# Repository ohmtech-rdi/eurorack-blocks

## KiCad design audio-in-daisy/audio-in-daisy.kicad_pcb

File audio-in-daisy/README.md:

# audio-in-daisy

## Description

This block is a simple analog audio input for the
[Daisy Seed](https://www.electro-smith.com/daisy/daisy) onboard codec.
Its design is detailed [here](./documentation/design.md).

## Connecting

- This block needs its `GND` to be connected to the ground. All `GND` pins are connected
   internally,
- This block needs its `-12` to be connected to the `-12V` of the `power-bus`,
- This block needs its `+12` to be connected to the `+12V` of the `power-bus`,
- The `NOP` pin can be either connected to:
   - `GND` to send (slightly noisy) zeros to the software implementation,
   - Cascading the `DI` signal from another `audio-in-daisy` block,
   - A pseudo-random predefined signal to detect a jack connection
      as explained on the Mutable Instruments forums
      [here](https://forum.mutable-instruments.net/t/plaits-normalization-probe/14358/2)
      and implemented
      [here](https://github.com/pichenettes/eurorack/blob/master/plaits/ui.cc#L368).
- The signal `OUT` is the audio input signal. It should be connected to either Pin 16 or Pin 17.
   See [Daisy Seed pinout](https://images.squarespace-cdn.com/content/v1/58d03fdc1b10e3bf442567b8/1591827747342-HCXMM2NNR26SP5F4U2CJ/ke17ZwdGBToddI8pDm48kN5PbQBGNYbW-5Hm1pf8hRF7gQa3H78H3Y0txjaiv_0fDoOvxcdMmMKkDsyUqMSsMWxHk725yiiHCCLfrh8O1z4YTzHvnKhyp6Da-NYroOW3ZGjoBKy3azqku80C789l0kLp48N9LluBiCpBrPZntaz462IffsVrAff3VJkwKncM1HZuDnV98dfxM9yHlqFkUQ/DaisyPinoutRev4%404x.png?format=500w) for details.

If only one audio input is connected, the other unused pin should be connected to `GND`.

The `DI` pin is the signal coming out directly from the jack connector and should be left floating
if not used.

The pseudo-random predefined signal jack detection method allows,
from a user experience point of view, to dissociate a non-connected
jack from a connected jack at `GND` level.

## Using

```c++
int main ()
{
   using namespace erb;
   
   Module module;
   AudioInDaisy audio_in_left (module, AudioInDaisyPinLeft);   // 1.
   AudioInDaisy audio_in_right (module, AudioInDaisyPinRight); // 2.

   module.run ([&](){
      for (size_t i = 0 ; i < audio_in_left.size () ; ++i)     // 3.
      {
         float left  = audio_in_left [i];                      // 4.
         float right = audio_in_right [i];                     // 5.
      }
   });
}
```

1. Attach the audio input to the module with the onboard codec left pin (Pin 16),
2. Attach the audio input to the module with the onboard codec right pin (Pin 17),
2. Loop through all the samples in the buffer. `erb::buffer_size` can be used instead,
3. Retrieve the audio input value on codec left pin,
4. Retrieve the audio input value on codec right pin.

The `AudioInDaisy` class reference is available [here](./documentation/reference.md).

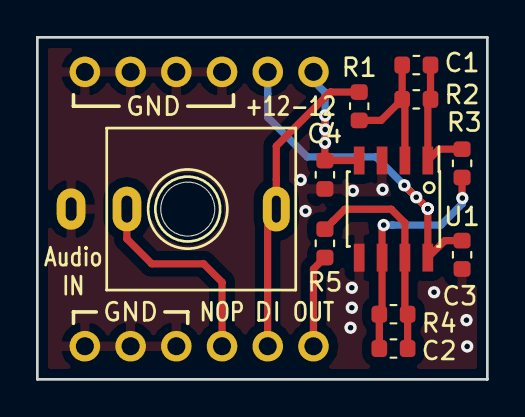
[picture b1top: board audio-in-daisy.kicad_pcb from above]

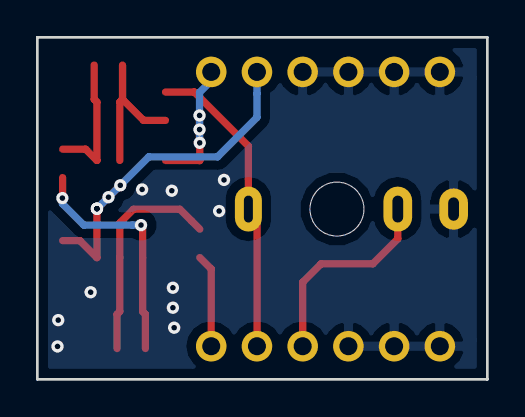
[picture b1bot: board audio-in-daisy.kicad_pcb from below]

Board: 2 copper layers, 25.0 x 19.0 mm, 13 parts (2 on the bottom side), 10 nets.

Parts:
C1: 47p; C_0603_1608Metric
C2: 560p; C_0603_1608Metric
C3, C4: 100n; C_0603_1608Metric
J1: IN; ThonkiconnJack
J2: OUT; PinHeader_1x06_P2.54mm_Vertical
J3: POWER; PinHeader_1x06_P2.54mm_Vertical
R1, R2, R3: 100k; R_0603_1608Metric
R4: 10k; R_0603_1608Metric
R5: 1k; R_0603_1608Metric
U1: TL072; SOIC-8_3.9x4.9mm_P1.27mm

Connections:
+12V: C3.1, J3.5, U1.8
-12V: C4.2, J3.6, U1.4
DI: J1.T, J2.2, R1.2
GND: C3.2, C4.1, J1.S, J2.4, J2.5, J2.6, J3.1, J3.2, J3.3, J3.4, U1.3, U1.5
NOP: J1.TN, J2.3
unnamed: C1.1, R2.1, R3.2, U1.1
unnamed: C1.2, R1.1, R2.2, U1.2
unnamed: C2.1, R4.1, R5.2, U1.7
unnamed: C2.2, R3.1, R4.2, U1.6
OUT: J2.1, R5.1

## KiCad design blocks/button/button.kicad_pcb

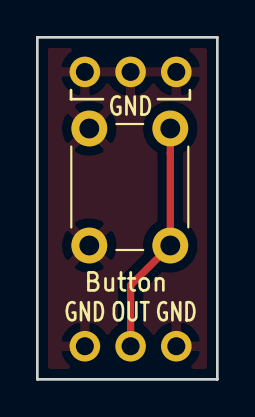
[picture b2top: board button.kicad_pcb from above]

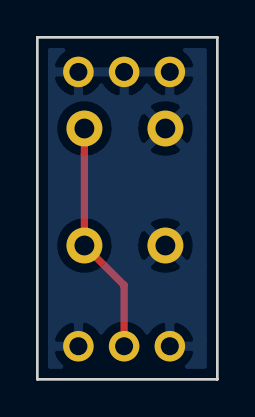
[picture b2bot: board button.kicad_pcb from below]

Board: 2 copper layers, 10.0 x 19.0 mm, 3 parts (2 on the bottom side), 2 nets.

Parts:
J1: POWER; PinHeader_1x03_P2.54mm_Vertical
J2: OUT; PinHeader_1x03_P2.54mm_Vertical
SW1: SW_Push_Dual; SW_PUSH_6mm_H7.3mm

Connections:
GND: J1.1, J1.2, J1.3, J2.1, J2.3, SW1.1
OUT: J2.2, SW1.2

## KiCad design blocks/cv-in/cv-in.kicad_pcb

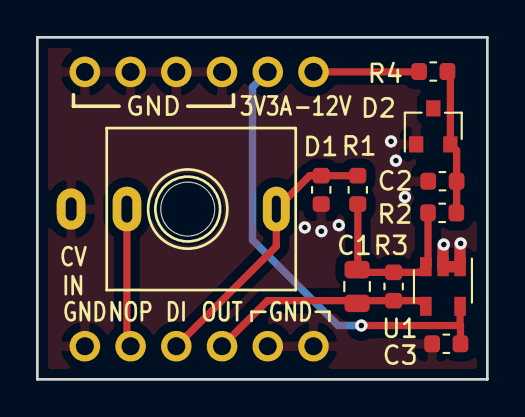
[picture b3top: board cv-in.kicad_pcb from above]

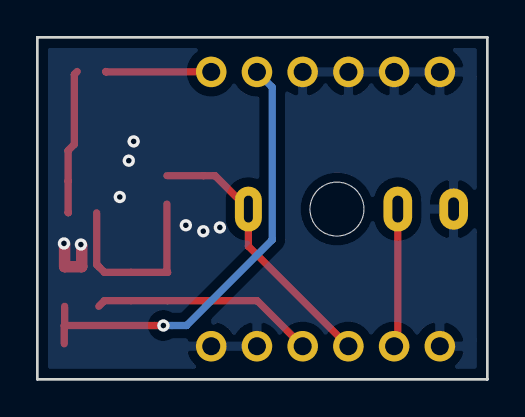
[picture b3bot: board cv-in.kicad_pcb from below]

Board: 2 copper layers, 25.0 x 19.0 mm, 13 parts (2 on the bottom side), 8 nets.

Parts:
C1: 33n; C_0805_2012Metric
C2: 1u; C_0603_1608Metric
C3: 100n; C_0603_1608Metric
D1: D_TVS; R_0603_1608Metric
D2: LM4040DBZ-10; SOT-23
J1: IN; ThonkiconnJack
J2: OUT; PinHeader_1x06_P2.54mm_Vertical
J3: POWER; PinHeader_1x06_P2.54mm_Vertical
R1: 100k; R_0603_1608Metric
R2: 120k; R_0603_1608Metric
R3: 20k; R_0603_1608Metric
R4: 4.99k; R_0603_1608Metric
U1: MCP6001U; SOT-23-5

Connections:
+3V3: C3.2, J3.5, U1.5
-12V: J3.6, R4.2
DI: D1.1, J1.T, J2.4, R1.2
GND: C2.1, C3.1, D1.2, D2.1, J1.S, J2.1, J2.2, J2.6, J3.1, J3.2, J3.3, J3.4, U1.1, U1.2
NOP: J1.TN, J2.5
unnamed: C1.2, R1.1, R2.1, R3.2, U1.3
OUT: C1.1, J2.3, R3.1, U1.4
VREF-10: C2.2, D2.2, R2.2, R4.1

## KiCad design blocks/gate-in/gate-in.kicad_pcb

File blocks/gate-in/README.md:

# gate-in

## Description

This block is a simple gate input.
Its design is detailed [here](./documentation/design.md).

## Connecting

- This block needs its `GND` to be connected to the ground. All `GND` pins are connected
   internally,
- This block needs its `3V3D` to be connected to the Daisy Seed 3V3 Digital Power I/O on Pin 38,
- The `NOP` pin can be either connected to:
   - `GND` to send zeros to the software implementation,
   - Cascading the `DI` signal from another `gate-in` block,
   - A pseudo-random predefined signal to detect a jack connection
      as explained on the Mutable Instruments forums
      [here](https://forum.mutable-instruments.net/t/plaits-normalization-probe/14358/2)
      and implemented
      [here](https://github.com/pichenettes/eurorack/blob/master/plaits/ui.cc#L368).
- The signal `OUT` is the Gate input signal. It should be connected to any Digital
   (and preferably non-Analog) GPIO
   of the target MCU. See [Daisy Seed pinout](https://images.squarespace-cdn.com/content/v1/58d03fdc1b10e3bf442567b8/1591827747342-HCXMM2NNR26SP5F4U2CJ/ke17ZwdGBToddI8pDm48kN5PbQBGNYbW-5Hm1pf8hRF7gQa3H78H3Y0txjaiv_0fDoOvxcdMmMKkDsyUqMSsMWxHk725yiiHCCLfrh8O1z4YTzHvnKhyp6Da-NYroOW3ZGjoBKy3azqku80C789l0kLp48N9LluBiCpBrPZntaz462IffsVrAff3VJkwKncM1HZuDnV98dfxM9yHlqFkUQ/DaisyPinoutRev4%404x.png?format=500w) for details.

The `DI` pin is the signal coming out directly from the jack connector and should be left floating
if not used.

The pseudo-random predefined signal jack detection method allows,
from a user experience point of view, to dissociate a non-connected
jack from a connected jack at `GND` level.

## Using

```c++
int main ()
{
   using namespace erb;
   
   Module module;
   GateIn gate_in (module, Pin7);   // 1.
   
   module.run ([&](){
      bool gate_value = gate_in;    // 2.
   });
}
```

1. Attach the gate to the module and specify the same digital pin as the one used for connecting,
2. Retrieve the boolean gate value.

The `GateIn` class reference is available [here](./documentation/reference.md).

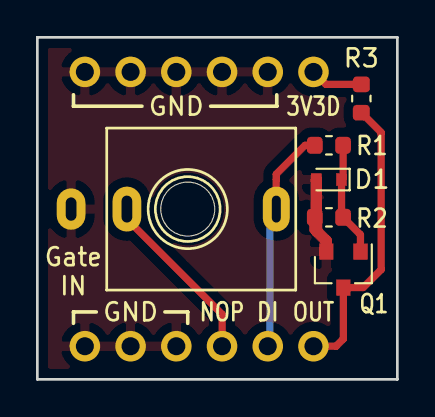
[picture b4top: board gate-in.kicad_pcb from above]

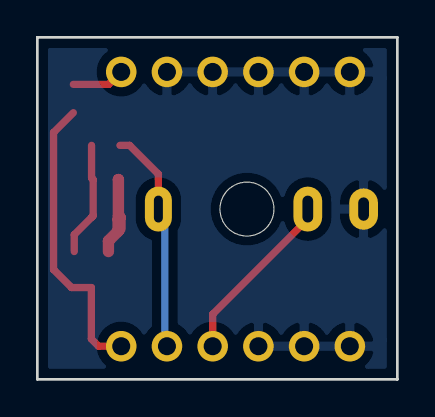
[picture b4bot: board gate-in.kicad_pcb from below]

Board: 2 copper layers, 20.0 x 19.0 mm, 8 parts (2 on the bottom side), 6 nets.

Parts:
D1: 1N4148; D_SOD-523
J1: IN; ThonkiconnJack
J2: OUT; PinHeader_1x06_P2.54mm_Vertical
J3: POWER; PinHeader_1x06_P2.54mm_Vertical
Q1: MMBT3904; SOT-23
R1, R2: 100k; R_0603_1608Metric
R3: 10k; R_0603_1608Metric

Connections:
+3V3: J3.6, R3.1
DI: J1.T, J2.2, R1.2
GND: D1.2, J1.S, J2.4, J2.5, J2.6, J3.1, J3.2, J3.3, J3.4, J3.5, Q1.2, R2.1
NOP: J1.TN, J2.3
unnamed: D1.1, Q1.1, R1.1, R2.2
OUT: J2.1, Q1.3, R3.2

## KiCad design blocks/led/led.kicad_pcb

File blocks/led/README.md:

# led

## Description

This block is a simple monochromatic LED.
Its design is detailed [here](./documentation/design.md).

## Connecting

- This block needs its `GND` to be connected to the ground. All `GND` pins are connected
   internally.
- The signal `IN` is the LED signal. It should be connected to any GPIO of the
   target MCU, **preferably non-analog** GPIOs. See [Daisy Seed pinout](https://images.squarespace-cdn.com/content/v1/58d03fdc1b10e3bf442567b8/1591827747342-HCXMM2NNR26SP5F4U2CJ/ke17ZwdGBToddI8pDm48kN5PbQBGNYbW-5Hm1pf8hRF7gQa3H78H3Y0txjaiv_0fDoOvxcdMmMKkDsyUqMSsMWxHk725yiiHCCLfrh8O1z4YTzHvnKhyp6Da-NYroOW3ZGjoBKy3azqku80C789l0kLp48N9LluBiCpBrPZntaz462IffsVrAff3VJkwKncM1HZuDnV98dfxM9yHlqFkUQ/DaisyPinoutRev4%404x.png?format=500w) for details.

## Using

```c++
int main ()
{
   using namespace erb;
   
   Module module;
   Led led (module, Pin23);   // 1.
   
   module.run ([&](){
      led.on ();              // 2.
      led.off ();             // 3.
      led.pulse ();           // 4.
      led.blink ();           // 5.
   });
}
```

1. Attach the LED to the module and specify the same pin as the one used for connecting,
2. The LED is turned on,
3. The LED is turned off,
4. The LED is shorlty pulsed,
5. The LED is blinking.

The `Led` class reference is available [here](./documentation/reference.md).

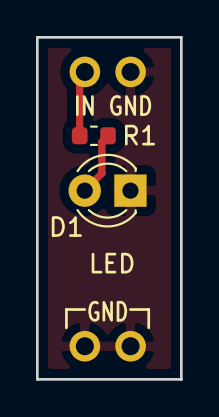
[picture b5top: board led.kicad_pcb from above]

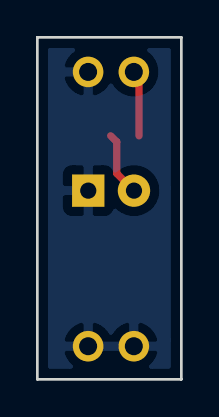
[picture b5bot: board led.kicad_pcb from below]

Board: 2 copper layers, 8.0 x 19.0 mm, 4 parts (2 on the bottom side), 3 nets.

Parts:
D1: LED; LED_D3.0mm
J1: IN; PinHeader_1x02_P2.54mm_Vertical
J2: GND; PinHeader_1x02_P2.54mm_Vertical
R1: 100; R_0603_1608Metric

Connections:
GND: D1.1, J1.2, J2.1, J2.2
IN: J1.1, R1.2
unnamed: D1.2, R1.1

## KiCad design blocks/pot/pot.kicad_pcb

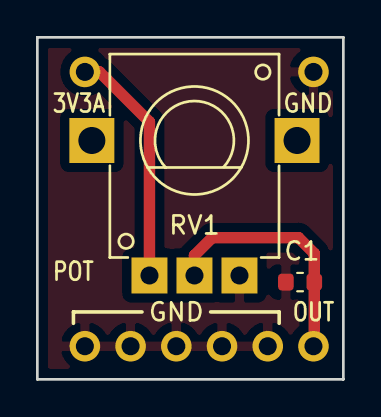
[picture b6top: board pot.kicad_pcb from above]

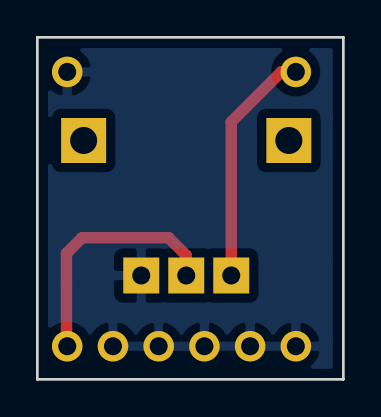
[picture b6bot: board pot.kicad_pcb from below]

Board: 2 copper layers, 17.0 x 19.0 mm, 5 parts (3 on the bottom side), 3 nets.

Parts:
C1: 100n; C_0603_1608Metric
J1: OUT; PinHeader_1x06_P2.54mm_Vertical
J2: GND; PinHeader_1x01_P2.54mm_Vertical
J3: 3V3; PinHeader_1x01_P2.54mm_Vertical
RV1: 100k; AlphaPot9ShaftD

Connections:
+3V3: J3.1, RV1.1
GND: C1.1, J1.2, J1.3, J1.4, J1.5, J1.6, J2.1, RV1.3
OUT: C1.2, J1.1, RV1.2
